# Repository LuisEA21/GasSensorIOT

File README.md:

# GasSensorIoT

# Descripción del dispositivo

Dispositivo electrónico de IoT para la medición de gases en el ambiente con los sensor MQ-2 y MQ-15. Además contiene un sensor para medir la temperatura y humedad del ambiente. La información de estos sensores es desplegada en tiempo real en una pantalla y son enviados a un servidor en la nube. Este dispositivo se compone de dos tarjetas electrónicas y un chasis impreso en 3D.

# Módulo de sensores

# Tarjeta de control ESP32

# Mapeo de Pines

## GasSensorIoT V1.0 

### Sensors
Dispositivo | GPIO 
--- | --- 
VCC | VBUS
D2 | 34
D1 | 35
A2 | 32
A1 | 33
GND | Ground

### NeoPixels
Dispositivo | GPIO 
--- | --- 
DataIn | 23
VCC | 3V3
GND | Ground

### Buzzer
Dispositivo | GPIO 
--- | --- 
Buzzer | 12

### Comunicación I2C (Sensor SHT30 y Pantalla)
Dispositivo | GPIO 
--- | --- 
VCC | 3V3
GND | Ground
SCL | 22
SDA | 21

### Comunicación UART
Dispositivo | GPIO 
--- | --- 
VCC | 3V3
GND | Ground
RX | RXD0
TX | TXD0

# Licencia

Hardware License: CERN OHL v1.0

Software License: GPL v3

Documentation License: CC BY 4.0 International

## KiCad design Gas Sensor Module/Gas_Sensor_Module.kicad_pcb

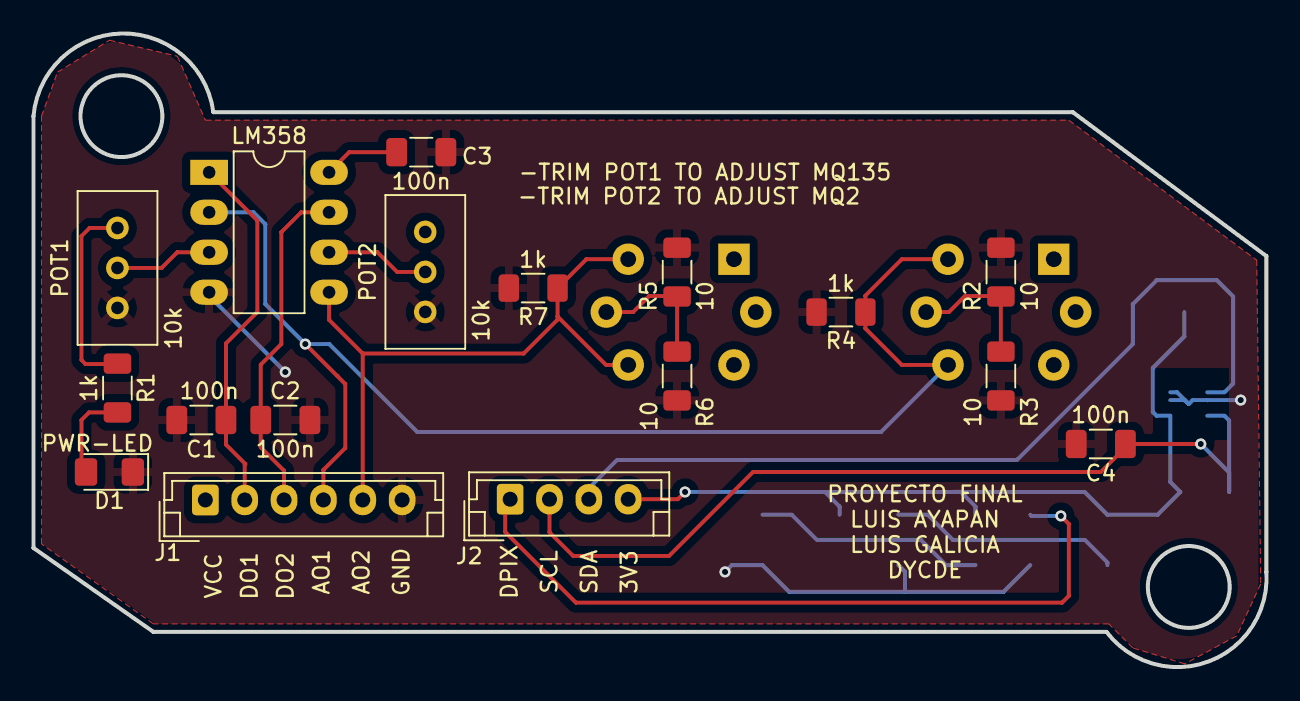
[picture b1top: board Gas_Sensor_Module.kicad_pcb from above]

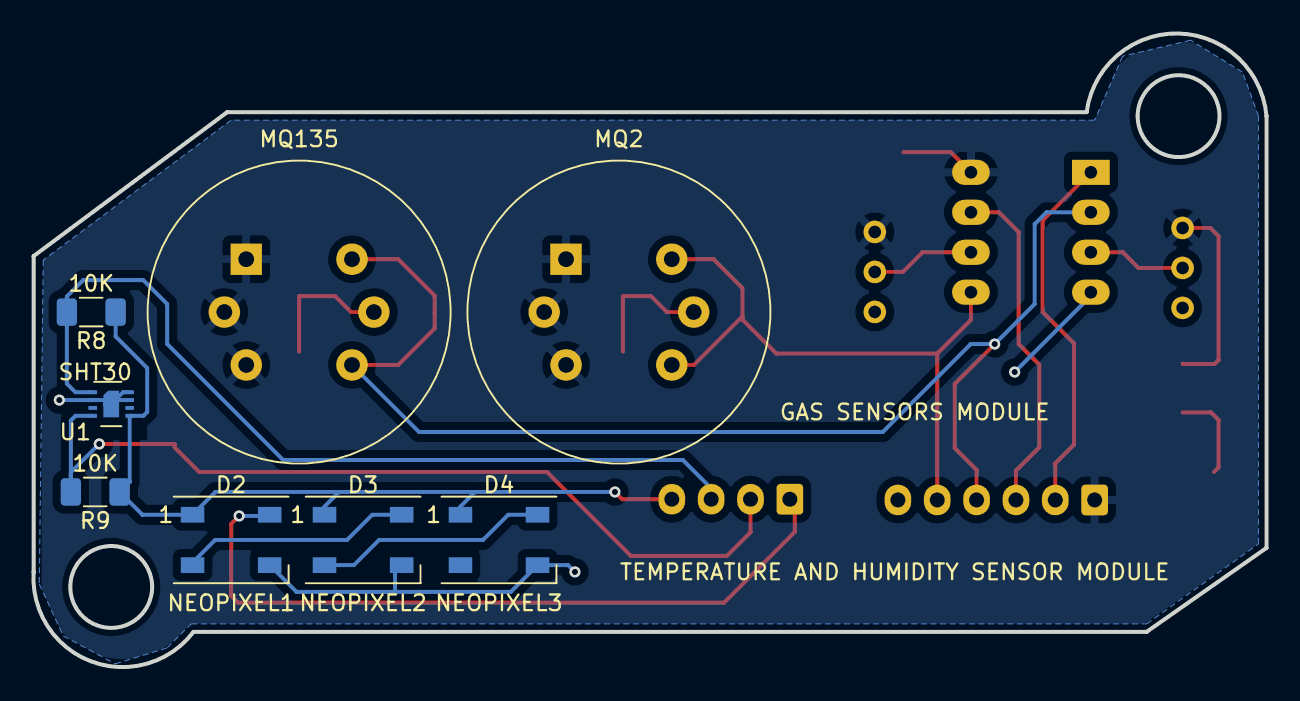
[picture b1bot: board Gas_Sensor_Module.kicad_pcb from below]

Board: 2 copper layers, 78.3 x 40.3 mm, 25 parts (8 on the bottom side), 17 nets.

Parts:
C1, C2, C3, C4: 100n; C_1206_3216Metric_Pad1.33x1.80mm_HandSolder
D1: PWR-LED; LED_1206_3216Metric_Pad1.42x1.75mm_HandSolder
D2: NEOPIXEL1; LED_WS2812B_PLCC4_5.0x5.0mm_P3.2mm
D3: NEOPIXEL2; LED_WS2812B_PLCC4_5.0x5.0mm_P3.2mm
D4: NEOPIXEL3; LED_WS2812B_PLCC4_5.0x5.0mm_P3.2mm
J1: Conn_01x06_Male; JST_EH_B6B-EH-A_1x06_P2.50mm_Vertical
J2: Conn_01x04_Male; JST_EH_B4B-EH-A_1x04_P2.50mm_Vertical
LM358: LM358; DIP-8_W7.62mm_LongPads
MQ2: MQ-2; MQ-6
MQ135: MQ-135; MQ-6
POT1, POT2: 10k; Potentiometer_Bourns_3296W_Vertical
R1, R4, R7: 1k; R_1206_3216Metric_Pad1.30x1.75mm_HandSolder
R2, R3, R5, R6: 10; R_1206_3216Metric_Pad1.30x1.75mm_HandSolder
R8, R9: 10K; R_1206_3216Metric_Pad1.30x1.75mm_HandSolder
U1: SHT30; Sensirion_DFN-8-1EP_2.5x2.5mm_P0.5mm_EP1.1x1.7mm

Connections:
/3V3: D2.1 (VDD), D3.1 (VDD), D4.1 (VDD), J2.4, R8.1, R9.1, U1.5 (VDD)
/AO1: J1.4, LM358.2 (-), MQ135.4 (A2), MQ135.6 (A1), R4.1
/AO2: J1.5, LM358.5 (+), MQ2.4 (A2), MQ2.6 (A1), R7.1
/DO1: C1.1, J1.2, LM358.1
/DO2: C2.1, J1.3, LM358.7
/DPIX: D2.4 (DIN), J2.1
/SCL: C4.1, J2.2, R9.2, U1.4 (SCL)
/SDA: J2.3, R8.2, U1.1 (SDA)
GND: C1.2, C2.2, C3.2, C4.2, D1.1 (K), D2.3 (VSS), D3.3 (VSS), D4.3 (VSS), J1.6, LM358.4 (V-), POT1.3, POT2.3, R2.2, R3.2, R4.2, R5.2, R6.2, R7.2, U1.2 (ADDR), U1.7 (R), U1.8 (VSS), U1.9 (VSS)
unnamed: D1.2 (A), R1.2
unnamed: D2.2 (DOUT), D3.4 (DIN)
unnamed: D3.2 (DOUT), D4.4 (DIN)
unnamed: LM358.3 (+), POT1.2
unnamed: LM358.6 (-), POT2.2
unnamed: MQ2.5 (VH-), R5.1, R6.1
unnamed: MQ135.5 (VH-), R2.1, R3.1
VCC: C3.1, J1.1, LM358.8 (V+), MQ2.1 (B1), MQ2.2 (VH+), MQ2.3 (B2), MQ135.1 (B1), MQ135.2 (VH+), MQ135.3 (B2), POT1.1, POT2.1, R1.1

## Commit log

2022-06-07 3D models
2022-06-07 Gas Sensors Module
2022-06-07 Final 3D designs
2022-06-07 Final 3D designs 2.0
2022-06-07 Final Gas Sensor Module
2022-06-07 Prueba
2022-06-07 Gas Sensor Module
2022-06-07 Esp32 files
